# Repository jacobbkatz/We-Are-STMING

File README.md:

# We-Are-STMING

**We Are STMing — 3D-Printed Scanning Tunneling Microscope**

A low-cost, 3D-printed Scanning Tunneling Microscope (STM), built from open-source designs and
documented for builders with no prior electronics or soldering experience.

This project combines two open-source lineages:

- **Mech Panda's `red-panda-stm`** — 3D-printed mechanics, firmware, and controller PCB design
- **Dan Berard's [home-built STM](https://dberard.com/home-built-stm/)** — scan head, tip
  preparation, and preamplifier design

The goal Nuh Shaheer and I share is a reproducible STM that anyone with a 3D printer and basic
tools can build, verify, and understand end to end.

---

## Status

**Paused, mid-build, with the instrument in pieces after a house move.**

Every subsystem a tunneling microscope needs is built, working and calibrated. The measurement
chain was checked end to end against a known resistor and agrees with Ohm's law to 0.13 of one
standard error. A real tip-and-sample junction was made and swept, and it behaves like a barrier
rather than a short.

**We detected tunneling. What we could not do is hold the gap steady long enough to take an
image** — with the motor off and nobody touching it, the surface moves by most of the scanner's
range within seconds. That measurement, and the five things that stood in the way, are written up
in full, along with the two results we published and later withdrew.

There is a plain-language write-up of the whole project at
**[jacobbkatz.github.io/We-Are-STMING](https://jacobbkatz.github.io/We-Are-STMING/)**.

**[`STATUS.md`](STATUS.md) is the live state of the build** — always current, rewritten at the end
of every work session. Read that rather than this paragraph, which will go stale.

---

## Start here

| If you want to | Read |
|---|---|
| Know where the build is right now | [`STATUS.md`](STATUS.md) |
| Build one yourself | [`docs/START_HERE_gotchas.md`](docs/START_HERE_gotchas.md), then [`docs/BOM.md`](docs/BOM.md) |
| Print the parts | [`CAD/prints/`](CAD/prints/) |
| Set up a computer to work on this | [`SETUP.md`](SETUP.md) |
| Follow the bring-up tests | [`docs/soft_launch_test_procedure.md`](docs/soft_launch_test_procedure.md) |
| Wire something up, or check a pinout | [`docs/WIRING.md`](docs/WIRING.md) |
| Send a command to the board | [`docs/COMMANDS.md`](docs/COMMANDS.md) |
| Help us close a gap | [`docs/OPEN_QUESTIONS.md`](docs/OPEN_QUESTIONS.md) |
| Find what is inside an archive | [`docs/INDEX.md`](docs/INDEX.md) |
| Understand the controller circuit | [`docs/UPSTREAM_MECHPANDA.md`](docs/UPSTREAM_MECHPANDA.md) |
| See how this compares to Berard's build | [`docs/UPSTREAM_BERARD.md`](docs/UPSTREAM_BERARD.md) |
| See what other DIY STM builders do | [`docs/OTHER_BUILDERS.md`](docs/OTHER_BUILDERS.md) |
| See what happened in past work sessions | [`sessions/`](sessions/) |

**`docs/START_HERE_gotchas.md` is not optional if you are building one.** Several of the things in
it cost real hardware if you get them wrong — including which pad the tip goes to, and which
connector is a power input rather than an output.

---

## Hardware overview

| System | Details |
|---|---|
| Frame | 3D-printed in PETG-CF for stiffness and dimensional stability. PA-CF was tried first for its lower thermal expansion but proved too difficult to print reliably at these tolerances. **Not PLA** — it creeps, and that shows up directly as drift |
| Vibration isolation | Platform suspended on tension springs, with eddy-current damping — an aluminum plate moving through fixed magnets, no contact |
| Coarse approach | 28BYJ-48 stepper motor through a ULN2003 driver board, wired directly to the Teensy |
| Scanner | Piezoelectric disc actuator with an **etched** tungsten tip &mdash; a bench supply through sodium hydroxide. (~~a cut tungsten tip, 0.25 mm wire cut at 45°~~ **corrected 2026-09-21: `SAID` Jacob, the tips were etched throughout, never cut**.) Roughly 680 nm of Z travel and 500 nm in X/Y, inferred from Berard's calibration of a similar disc |
| Coarse approach step | About **7.8 nm** per motor step — 1/4"-80 screw, 2048 steps/rev, ~20x lever reduction. Lever ratio still to be verified on our geometry |
| Sample | Gold foil, mounted on a magnetic disc with a conductive path to the bias magnet |
| Preamplifier | OPA627-based transimpedance amplifier with a 100 MΩ feedback resistor, mounted close to the tip to preserve the picoamp-level tunneling signal |
| Controller | Teensy 4.1 driving four AD5761 DACs over SPI — X, Y and sample bias at ±3 V, Z at ±10 V — and reading tunneling current via an LTC2326-16 ADC on a second SPI bus |
| Power | ±18 V in to the controller board, which generates the ±15 V rails it sends out to the preamplifier |

---

## Repository layout

```
STATUS.md      Live state of the build. Read this first
CLAUDE.md      Working protocol, followed automatically by Claude Code
SETUP.md       How to set up a computer to work on this project
sessions/      One log per work session, newest supersedes older
docs/          Gotchas, BOM, wiring, commands, and project history
Code/teensy/   Teensy 4.1 firmware (PlatformIO)
Code/pc/       Python tools that talk to the board over serial
CAD/prints/    Every printable part as STL - GitHub previews these in the browser
CAD/           Fusion 360 source
PCB/           Controller board design files
gerbers/       Manufacturing files for the controller and preamp boards
our_preamp_cad_files/   Our own modified preamp enclosure
```

---

## How we work on this

This is built by two people on two computers, both using Claude Code, with **GitHub as the single
source of truth.** Each session pulls the latest state at the start and pushes back at the end, so
neither machine works from stale findings. The protocol is in [`CLAUDE.md`](CLAUDE.md); the
one-time setup is in [`SETUP.md`](SETUP.md).

That matters more here than it sounds. Several findings in this project were later proven wrong,
and acting on a superseded one has already cost hardware time. `STATUS.md` and the dated session
logs exist so that the newest correction always wins.

---

## Why this design

This build follows the philosophy of both source projects: get real atomic-resolution imaging out
of a machine built primarily from a 3D printer, off-the-shelf electronics, and hand soldering,
without requiring a machine shop or specialized fabrication.

Everything here is documented so someone with no prior STM, electronics, or soldering background
can follow it — including the reasoning behind each part choice, not just the instructions. Where
something genuinely isn't documented in any source we could find, it is marked **UNKNOWN** or
**VERIFY** rather than guessed. A confident wrong number is worse than an admitted gap.

---

## Acknowledgments

This project would not exist without the prior open-source work of:

- **Dan Berard** — [dberard.com/home-built-stm](https://dberard.com/home-built-stm/)
- **Mech Panda** — `red-panda-stm`

Thank you also to Dr. Percy Zahl (Brookhaven National Laboratory, CFN) for guidance on vibration
isolation and scan head design.

---

## Contributing

This is an active build log as much as a finished project. Corrections, suggestions and questions
are welcome, especially from anyone who has built a similar instrument.

The **What we still don't know** section of [`docs/BOM.md`](docs/BOM.md) and the open questions in
[`STATUS.md`](STATUS.md) are the most useful places to help. If you work one of them out while
building, please open an issue — closing those gaps is most of what this project is for.

---

## License

**Copyright (c) 2026 Jacob Katz and Nuh Shaheer. All rights reserved.**
See [`LICENSE`](LICENSE).

This repository is public so it can be **read**, not so it can be reused without asking. Reading,
cloning, quoting and citing it need no permission. **Redistributing it, building a derivative of
it, or using it commercially need ours first** — write to jacob@quis.com, and expect a yes.

**Parts of this repository are not ours to license.** The mechanics, controller and firmware follow
**Mech Panda's `red-panda-stm`**; the scan head, tip preparation and preamplifier follow
**[Dan Berard's home-built STM](https://dberard.com/home-built-stm/)**. Their designs are theirs.
Two firmware files carry Daniel Berard's own MIT notice, retained unaltered, and the Inter typeface
in the figures directory is under the SIL Open Font License. `LICENSE` names each one.

Every measurement, figure and raw file here stays free to read. The record is the point.

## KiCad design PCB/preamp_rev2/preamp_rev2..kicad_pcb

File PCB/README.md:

# PCB design files

Archives, so you can see what is in each without downloading it.

| File | Contains |
|---|---|
| `Altium_Scanning Tunneling Microscope_2023-11-04.zip` | Altium source for the controller board — ADC, connectors, DAC and power schematic sheets |
| `PDF_Scanning Tunneling Microscope_2023-11-04.zip` | The same schematics as PDF. **Start here if you just want to read the circuit** |
| `STMP_easyEDA.zip` | EasyEDA project for the controller board |
| `preamp_rev2/` | **KiCad 10 project for preamp rev 2**, made by Nuh 2026-10-13 from Berard's Eagle board. **UNTESTED** — its gerbers and the full account are in [`../gerbers/README.md`](../gerbers/README.md). Open `preamp_rev2..kicad_pro` in KiCad 10 (the double dot is in the project's name; KiCad needs all three files named alike). The schematic file is empty: only the board was imported. `LICENSE_Berard_MIT.txt` travels with it because the layout is his |

Manufacturing files are in [`../gerbers/`](../gerbers/). Verified pinouts, LED meanings, the power
tree and the output stage are in [`../docs/WIRING.md`](../docs/WIRING.md) — use that rather than
re-deriving them from the schematic.

The preamplifier is a separate board. Its Eagle source ships inside
`We-Are-STMING_PCB.zip` in the repository root, under `preamplifier/eagle/`, and is
**MIT licensed** by its original author.

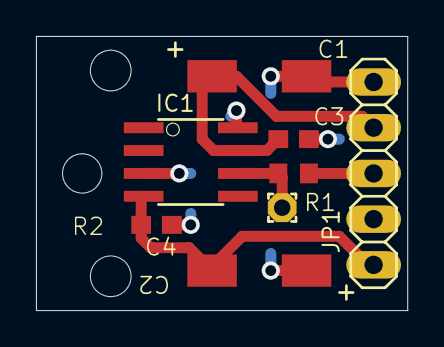
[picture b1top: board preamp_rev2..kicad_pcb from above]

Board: 2 copper layers, 20.6 x 15.2 mm, 11 parts (0 on the bottom side), 5 nets.

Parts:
C1, C2: 4.7uF; C_6032-28W
C3, C4: 0.1uF; C0603
IC1: OPA627AU; SO08
JP1: 1X05
PAD1: 1,6_0,9
R1: 220; R0603
UNK_HOLE_0: dummyfp0
UNK_HOLE_1: dummyfp1
UNK_HOLE_2: dummyfp2

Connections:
+9V: C1.+, C3.1, IC1.7, JP1.2
-9V: C2.-, C4.1, IC1.4, JP1.5
GND: C1.-, C2.+, C3.2, C4.2, IC1.3, IC1.8, JP1.1, JP1.4
unnamed: IC1.6, PAD1.1, R1.1
unnamed: JP1.3, R1.2
